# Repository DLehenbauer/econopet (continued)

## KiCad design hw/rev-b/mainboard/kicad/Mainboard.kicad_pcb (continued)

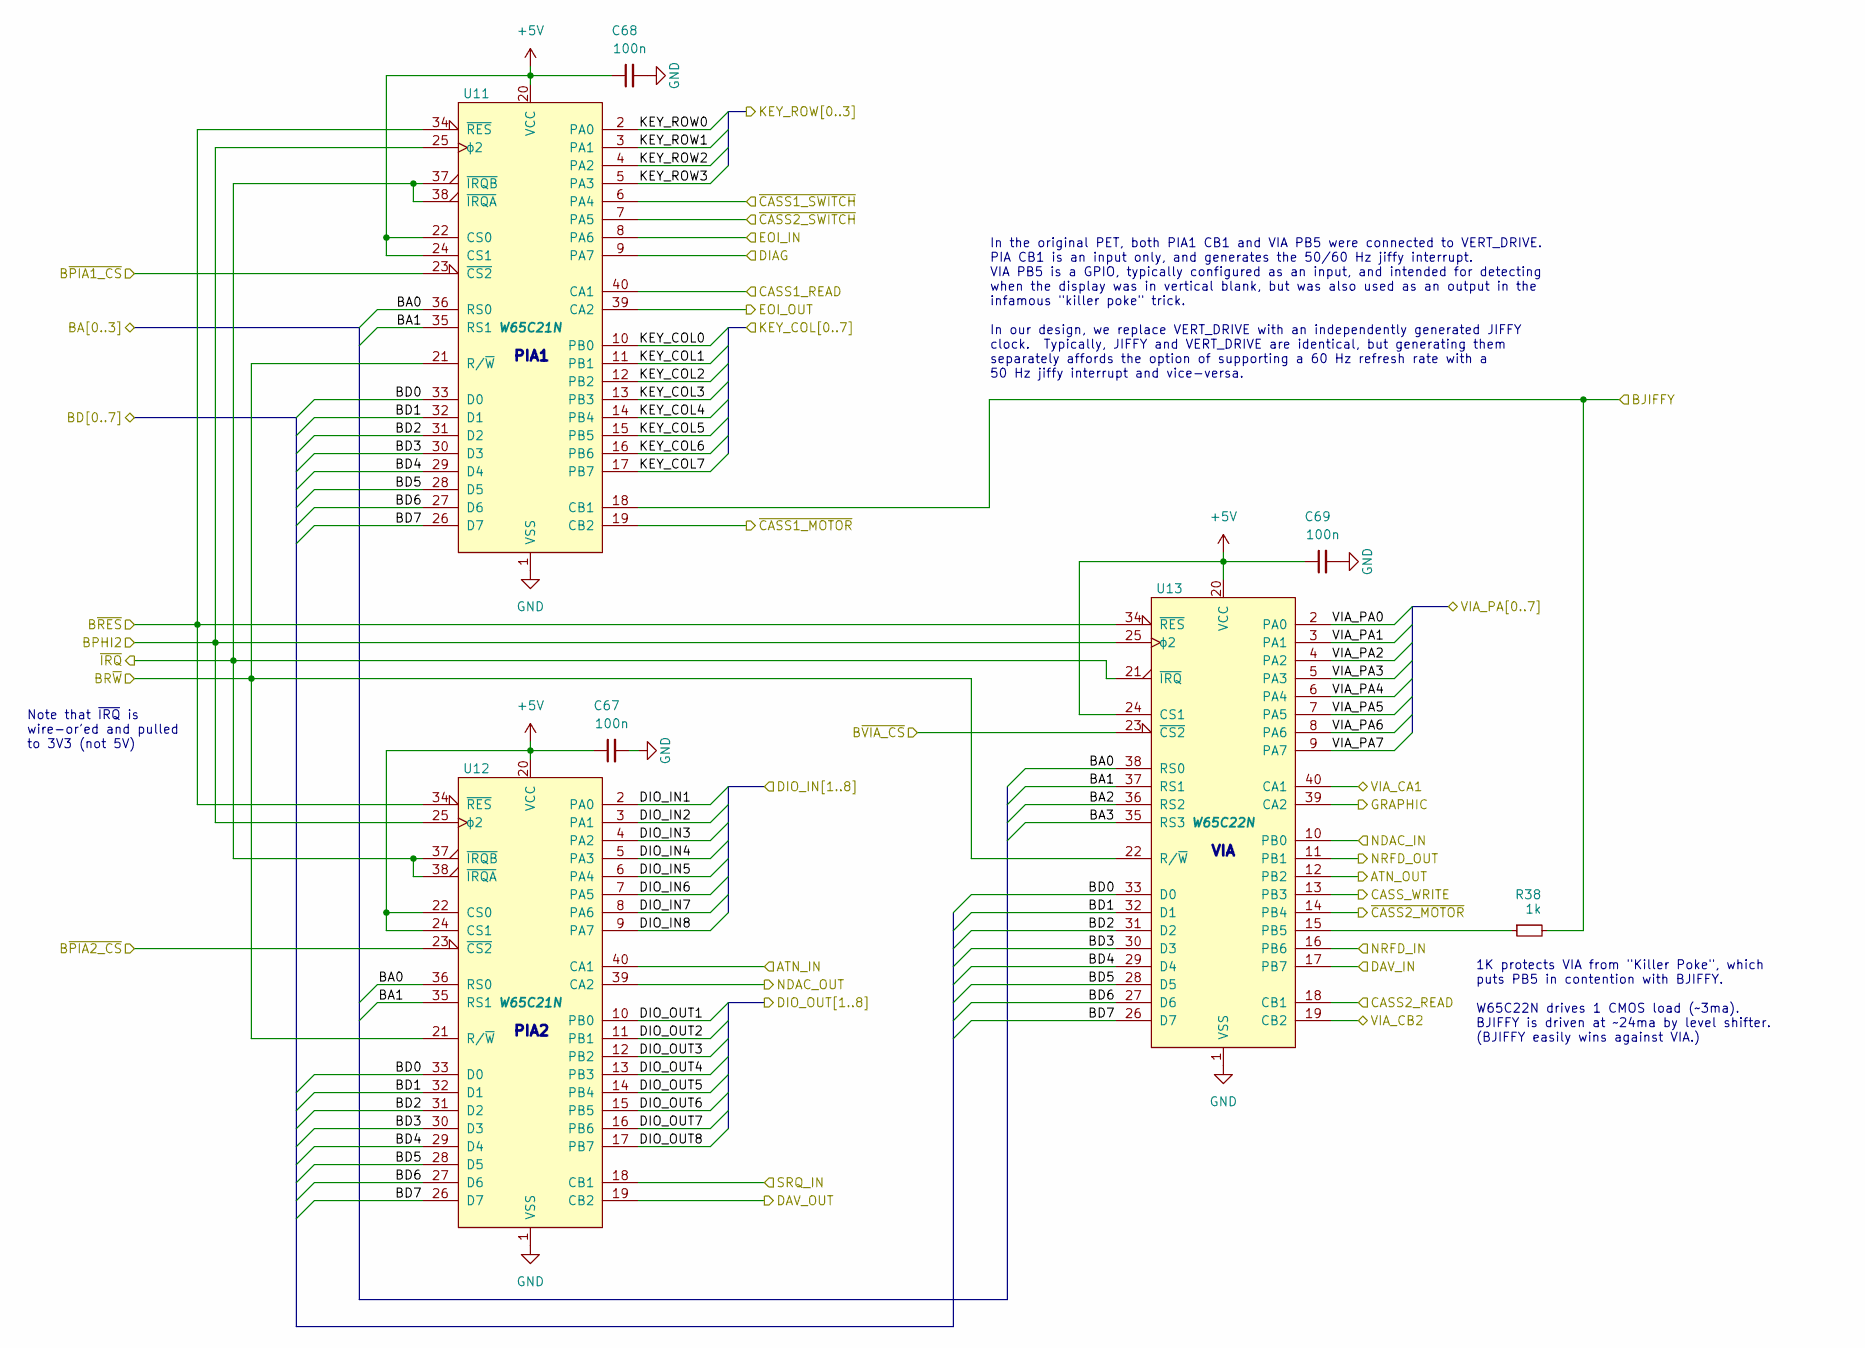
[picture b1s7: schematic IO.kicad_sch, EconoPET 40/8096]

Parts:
C67, C68, C69: 100n; C_0402_1005Metric; LCSC Part # C307331
R38: 1k; R_0402_1005Metric; LCSC Part # C11702
U11, U12: W65C21N; DIP-40_W15.24mm_Socket; MOUSER 955-W65C21N6TPG-14,571-1-2199299-5
U13: W65C22N; DIP-40_W15.24mm_Socket; MOUSER 955-W65C22N6TPG-14,571-1-2199299-5

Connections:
+5V: C67.1, C68.1, C69.1, U11.20 (VCC), U11.22 (CS0), U11.24 (CS1), U12.20 (VCC), U12.22 (CS0), U12.24 (CS1), U13.20 (VCC), U13.24 (CS1); also elsewhere on the board
/CASS/CASS1_READ: U11.40 (CA1); also elsewhere on the board
/CASS/CASS2_READ: U13.18 (CB1); also elsewhere on the board
/CASS/CASS_WRITE: U13.13 (PB3); also elsewhere on the board
/CASS/~CASS1_MOTOR: U11.19 (CB2); also elsewhere on the board
/CASS/~CASS1_SWITCH: U11.6 (PA4); also elsewhere on the board
/CASS/~CASS2_MOTOR: U13.14 (PB4); also elsewhere on the board
/CASS/~CASS2_SWITCH: U11.7 (PA5); also elsewhere on the board
/IEEE/ATN_IN: U12.40 (CA1); also elsewhere on the board
/IEEE/ATN_OUT: U13.12 (PB2); also elsewhere on the board
/IEEE/DAV_IN: U13.17 (PB7); also elsewhere on the board
/IEEE/DAV_OUT: U12.19 (CB2); also elsewhere on the board
/IEEE/DIO_IN1: U12.2 (PA0); also elsewhere on the board
/IEEE/DIO_IN2: U12.3 (PA1); also elsewhere on the board
/IEEE/DIO_IN3: U12.4 (PA2); also elsewhere on the board
/IEEE/DIO_IN4: U12.5 (PA3); also elsewhere on the board
/IEEE/DIO_IN5: U12.6 (PA4); also elsewhere on the board
/IEEE/DIO_IN6: U12.7 (PA5); also elsewhere on the board
/IEEE/DIO_IN7: U12.8 (PA6); also elsewhere on the board
/IEEE/DIO_IN8: U12.9 (PA7); also elsewhere on the board
/IEEE/DIO_OUT1: U12.10 (PB0); also elsewhere on the board
/IEEE/DIO_OUT2: U12.11 (PB1); also elsewhere on the board
/IEEE/DIO_OUT3: U12.12 (PB2); also elsewhere on the board
/IEEE/DIO_OUT4: U12.13 (PB3); also elsewhere on the board
/IEEE/DIO_OUT5: U12.14 (PB4); also elsewhere on the board
/IEEE/DIO_OUT6: U12.15 (PB5); also elsewhere on the board
/IEEE/DIO_OUT7: U12.16 (PB6); also elsewhere on the board
/IEEE/DIO_OUT8: U12.17 (PB7); also elsewhere on the board
/IEEE/EOI_IN: U11.8 (PA6); also elsewhere on the board
/IEEE/EOI_OUT: U11.39 (CA2); also elsewhere on the board
/IEEE/IFC_OUT: U11.34 (~RES), U12.34 (~RES), U13.34 (~RES); also elsewhere on the board
/IEEE/NDAC_IN: U13.10 (PB0); also elsewhere on the board
/IEEE/NDAC_OUT: U12.39 (CA2); also elsewhere on the board
/IEEE/NRFD_IN: U13.16 (PB6); also elsewhere on the board
/IEEE/NRFD_OUT: U13.11 (PB1); also elsewhere on the board
/IEEE/SRQ_IN: U12.18 (CB1); also elsewhere on the board
/IO/BA0: U11.36 (RS0), U12.36 (RS0), U13.38 (RS0); also elsewhere on the board
/IO/BA1: U11.35 (RS1), U12.35 (RS1), U13.37 (RS1); also elsewhere on the board
/IO/BA2: U13.36 (RS2); also elsewhere on the board
/IO/BA3: U13.35 (RS3); also elsewhere on the board
/IO/BD0: U11.33 (D0), U12.33 (D0), U13.33 (D0); also elsewhere on the board
/IO/BD1: U11.32 (D1), U12.32 (D1), U13.32 (D1); also elsewhere on the board
/IO/BD2: U11.31 (D2), U12.31 (D2), U13.31 (D2); also elsewhere on the board
/IO/BD3: U11.30 (D3), U12.30 (D3), U13.30 (D3); also elsewhere on the board
/IO/BD4: U11.29 (D4), U12.29 (D4), U13.29 (D4); also elsewhere on the board
/IO/BD5: U11.28 (D5), U12.28 (D5), U13.28 (D5); also elsewhere on the board
/IO/BD6: U11.27 (D6), U12.27 (D6), U13.27 (D6); also elsewhere on the board
/IO/BD7: U11.26 (D7), U12.26 (D7), U13.26 (D7); also elsewhere on the board
/IO/BJIFFY: R38.2, U11.18 (CB1); also elsewhere on the board
/IO/BPHI2: U11.25 (ϕ2), U12.25 (ϕ2), U13.25 (ϕ2); also elsewhere on the board
/IO/BR~W: U11.21 (R/~W), U12.21 (R/~W), U13.22 (R/~W); also elsewhere on the board
/IO/B~PIA1_CS: U11.23 (~CS2); also elsewhere on the board
/IO/B~PIA2_CS: U12.23 (~CS2); also elsewhere on the board
/IO/B~VIA_CS: U13.23 (~CS2); also elsewhere on the board
/IO/DIAG: U11.9 (PA7); also elsewhere on the board
/IO/GRAPHIC: U13.39 (CA2); also elsewhere on the board
/IO/KEY_COL0: U11.10 (PB0); also elsewhere on the board
/IO/KEY_COL1: U11.11 (PB1); also elsewhere on the board
/IO/KEY_COL2: U11.12 (PB2); also elsewhere on the board
/IO/KEY_COL3: U11.13 (PB3); also elsewhere on the board
/IO/KEY_COL4: U11.14 (PB4); also elsewhere on the board
/IO/KEY_COL5: U11.15 (PB5); also elsewhere on the board
/IO/KEY_COL6: U11.16 (PB6); also elsewhere on the board
/IO/KEY_COL7: U11.17 (PB7); also elsewhere on the board
/IO/KEY_ROW0: U11.2 (PA0); also elsewhere on the board
/IO/KEY_ROW1: U11.3 (PA1); also elsewhere on the board
/IO/KEY_ROW2: U11.4 (PA2); also elsewhere on the board
/IO/KEY_ROW3: U11.5 (PA3); also elsewhere on the board
/IO/VIA_CA1: U13.40 (CA1); also elsewhere on the board
/IO/VIA_CB2: U13.19 (CB2); also elsewhere on the board
/IO/VIA_PA0: U13.2 (PA0); also elsewhere on the board
/IO/VIA_PA1: U13.3 (PA1); also elsewhere on the board
/IO/VIA_PA2: U13.4 (PA2); also elsewhere on the board
/IO/VIA_PA3: U13.5 (PA3); also elsewhere on the board
/IO/VIA_PA4: U13.6 (PA4); also elsewhere on the board
/IO/VIA_PA5: U13.7 (PA5); also elsewhere on the board
/IO/VIA_PA6: U13.8 (PA6); also elsewhere on the board
/IO/VIA_PA7: U13.9 (PA7); also elsewhere on the board
/MAGIC/FPGA/~IRQ: U11.37 (~IRQB), U11.38 (~IRQA), U12.37 (~IRQB), U12.38 (~IRQA), U13.21 (~IRQ); also elsewhere on the board
GND: C67.2, C68.2, C69.2, U11.1 (VSS), U12.1 (VSS), U13.1 (VSS); also elsewhere on the board
unnamed: R38.1, U13.15 (PB5)

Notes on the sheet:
1K protects VIA from "Killer Poke", which puts PB5 in contention with BJIFFY. W65C22N drives 1 CMOS load (~3ma). BJIFFY is driven at ~24ma by level shifter. (BJIFFY easily wins against VIA.)
In the original PET, both PIA1 CB1 and VIA PB5 were connected to VERT_DRIVE. PIA CB1 is an input only, and generates the 50/60 Hz jiffy interrupt. VIA PB5 is a GPIO, typically configured as an input, and intended for detecting when the display was in vertical blank, but was also used as an output i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
PIA1
PIA2
Note that ~{IRQ} is wire-or'ed and pulled to 3V3 (not 5V)
VIA

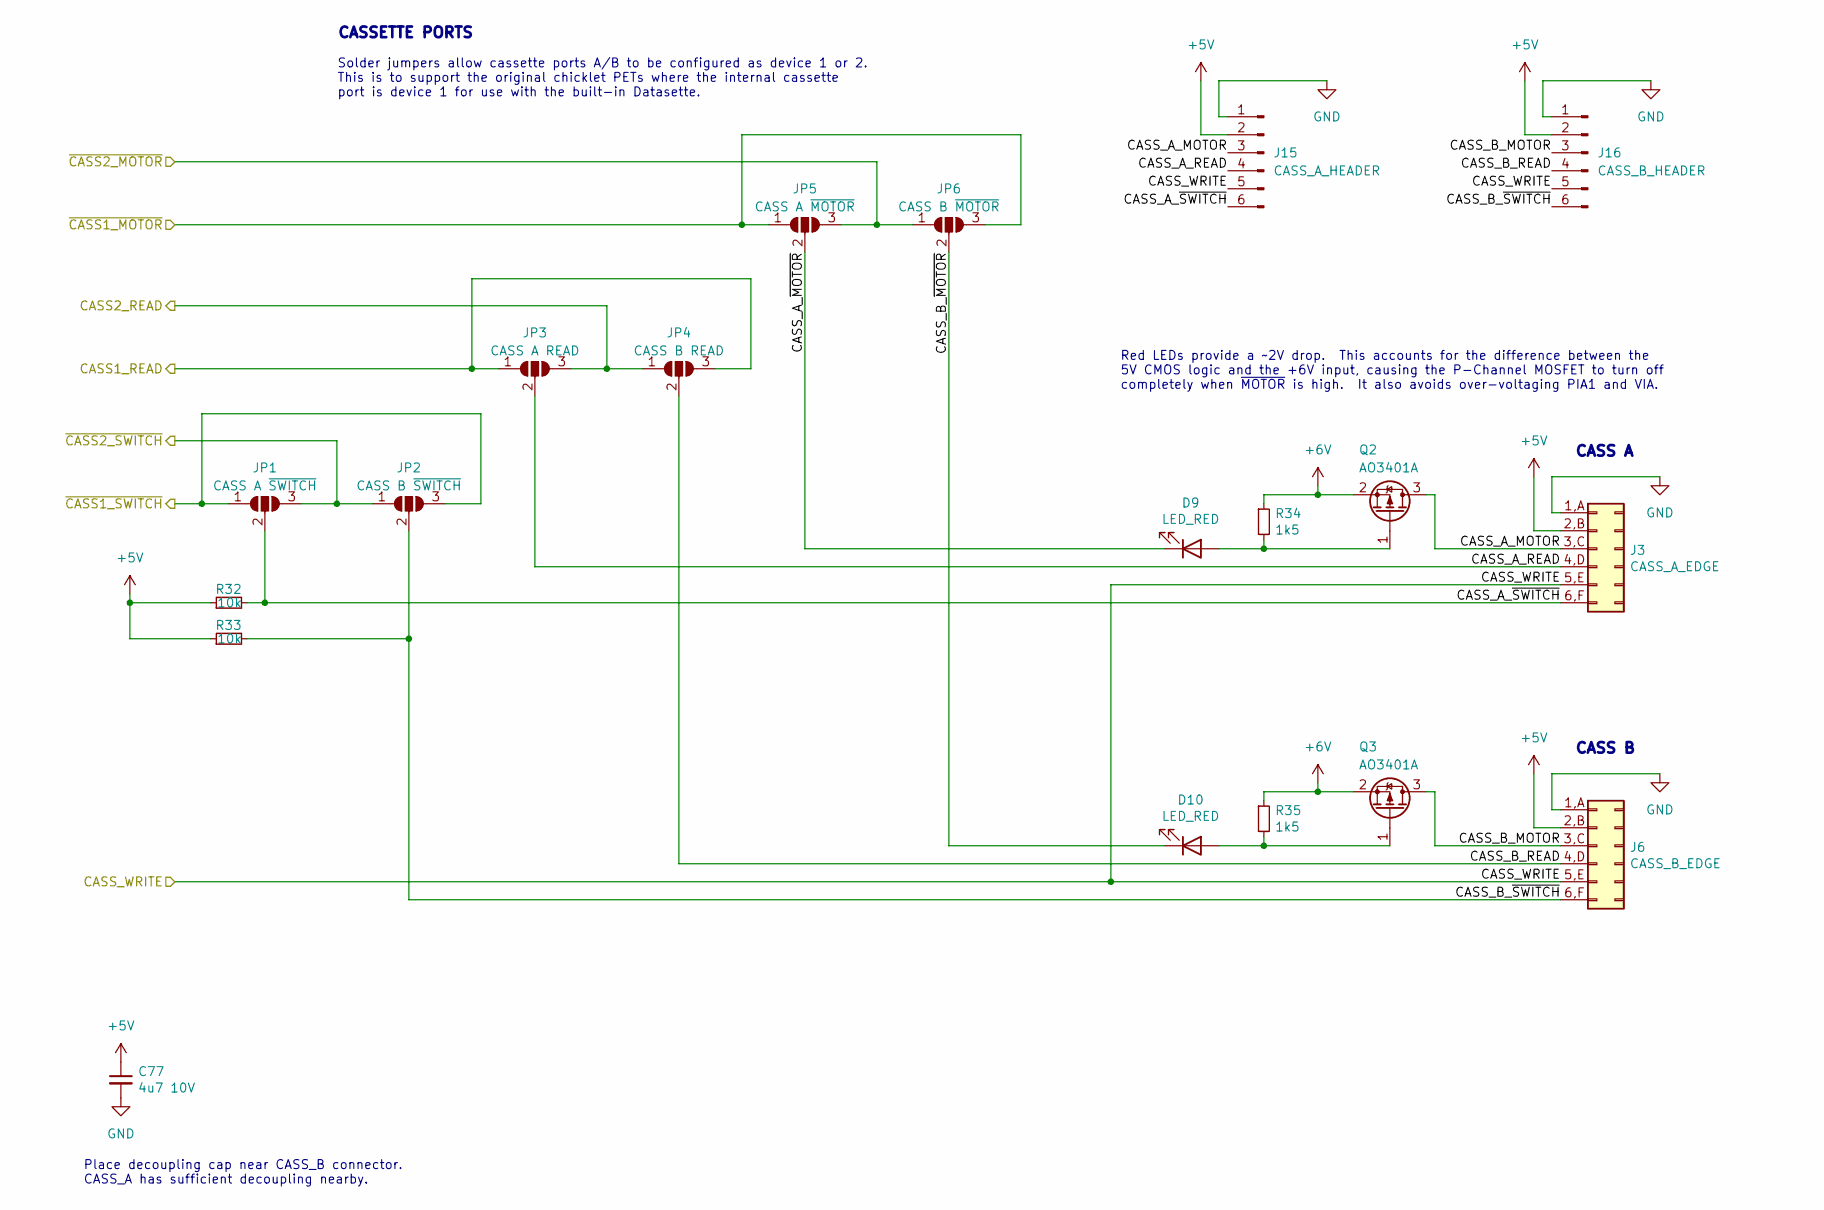
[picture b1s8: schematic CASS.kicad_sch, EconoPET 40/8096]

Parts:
C77: 4u7 10V; C_0402_1005Metric; LCSC Part # C23733
D9, D10: LED_RED; LED_0603_1608Metric; LCSC Part # C2286
J3: CASS_A_EDGE; CBM_PET_CASS_EDGE_CON_12P
J6: CASS_B_EDGE; CBM_PET_CASS_EDGE_CON_12P
J15: CASS_A_HEADER; PinHeader_1x06_P2.54mm_Vertical; MOUSER 649-1012937891002BLF
J16: CASS_B_HEADER; PinHeader_1x06_P2.54mm_Vertical; MOUSER 649-1012937891002BLF
JP1: CASS A ~{SWITCH}; SolderJumper-3_P1.3mm_Open_RoundedPad1.0x1.5mm
JP2: CASS B ~{SWITCH}; SolderJumper-3_P1.3mm_Open_RoundedPad1.0x1.5mm
JP3: CASS A READ; SolderJumper-3_P1.3mm_Open_RoundedPad1.0x1.5mm
JP4: CASS B READ; SolderJumper-3_P1.3mm_Open_RoundedPad1.0x1.5mm
JP5: CASS A ~{MOTOR}; SolderJumper-3_P1.3mm_Open_RoundedPad1.0x1.5mm
JP6: CASS B ~{MOTOR}; SolderJumper-3_P1.3mm_Open_RoundedPad1.0x1.5mm
Q2, Q3: AO3401A; SOT-23_L2.9-W1.3-P1.90-LS2.4-BR; LCSC Part # C15127
R32, R33: 10k; R_0402_1005Metric; LCSC Part # C25744
R34, R35: 1k5; R_0402_1005Metric; LCSC Part # C25867

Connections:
+5V: C77.1, J3.2,B (+5V), J6.2,B (+5V), J15.2, J16.2, R32.1, R33.1; also elsewhere on the board
+6V: Q2.2 (S), Q3.2 (S), R34.1, R35.1; also elsewhere on the board
/CASS/CASS1_READ: JP3.1 (A), JP4.3 (B); also elsewhere on the board
/CASS/CASS2_READ: JP3.3 (B), JP4.1 (A); also elsewhere on the board
/CASS/CASS_A_MOTOR: J3.3,C (MOTOR), J15.3, Q2.3 (D)
/CASS/CASS_A_READ: J3.4,D (READ), J15.4, JP3.2 (C)
/CASS/CASS_A_~MOTOR: D9.1 (K), JP5.2 (C)
/CASS/CASS_A_~SWITCH: J3.6,F (SWITCH), J15.6, JP1.2 (C), R32.2
/CASS/CASS_B_MOTOR: J6.3,C (MOTOR), J16.3, Q3.3 (D)
/CASS/CASS_B_READ: J6.4,D (READ), J16.4, JP4.2 (C)
/CASS/CASS_B_~MOTOR: D10.1 (K), JP6.2 (C)
/CASS/CASS_B_~SWITCH: J6.6,F (SWITCH), J16.6, JP2.2 (C), R33.2
/CASS/CASS_WRITE: J3.5,E (WRITE), J6.5,E (WRITE), J15.5, J16.5; also elsewhere on the board
/CASS/~CASS1_MOTOR: JP5.1 (A), JP6.3 (B); also elsewhere on the board
/CASS/~CASS1_SWITCH: JP1.1 (A), JP2.3 (B); also elsewhere on the board
/CASS/~CASS2_MOTOR: JP5.3 (B), JP6.1 (A); also elsewhere on the board
/CASS/~CASS2_SWITCH: JP1.3 (B), JP2.1 (A); also elsewhere on the board
GND: C77.2, J3.1,A (GND), J6.1,A (GND), J15.1, J16.1; also elsewhere on the board
unnamed: D9.2 (A), Q2.1 (G), R34.2
unnamed: D10.2 (A), Q3.1 (G), R35.2

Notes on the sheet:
Solder jumpers allow cassette ports A/B to be configured as device 1 or 2. This is to support the original chicklet PETs where the internal cassette port is device 1 for use with the built-in Datasette.
CASS B
Red LEDs provide a ~2V drop. This accounts for the difference between the 5V CMOS logic and the +6V input, causing the P-Channel MOSFET to turn off completely when ~{MOTOR} is high. It also avoids over-voltaging PIA1 and VIA.
CASS A
Place decoupling cap near CASS_B connector. CASS_A has sufficient decoupling nearby.
CASSETTE PORTS

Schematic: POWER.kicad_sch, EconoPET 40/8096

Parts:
C7, C14, C18, C25, C27, C28, C89: 100n; C_0402_1005Metric; LCSC Part # C307331
C9, C10, C85: 22n; C_0402_1005Metric; LCSC Part # C1532
C11, C19, C22, C24, C29: 22u; C_0805_2012Metric; LCSC Part # C45783
C12, C13, C15, C16: 10u; C_0603_1608Metric; LCSC Part # C96446
C17, C21: 33p; C_0402_1005Metric; LCSC Part # C1562
C20: 1u; C_0402_1005Metric; LCSC Part # C52923
C23, C26, C30, C31: 4u7 10V; C_0402_1005Metric; LCSC Part # C23733
C108, C109: 10u 16V; CP_EIA-3216-18_Kemet-A; LCSC Part # C7171
C110: 15000uF; CP_Radial_D18.0mm_P5.00mm_P7.50mm; MOUSER 661-BV250L153AM40S; not fitted
C111, C112: 2200uF; CP_Radial_D12.5mm_P5.00mm; MOUSER 232-25PK2200MEFC125X
D1, D2, D3: SS54; D_SMA; LCSC Part # C22452
D4: SM4007; D_SOD-123F; LCSC Part # C64898
D6: LED_RED; LED_0603_1608Metric; LCSC Part # C2286
FB1: 600 200ma; L_0603_1608Metric; LCSC Part # C1002
H1: MountingHole_Pad; MountingHole_4mm_Pad
J8: PET POWER; PET_POWER_Molex_KK-396_A-41791-0009_1x09_P3.96mm_Vertical; MOUSER 571-6403849
J10: 5V PWR; PinHeader_2x03_P2.54mm_Vertical; MOUSER 649-1012938195002BLF
J11: 9V POWER; PinHeader_1x02_P2.54mm_Vertical; MOUSER 649-1012937891002BLF
J13: 9V POWER JACK; BarrelJack_Horizontal; MOUSER 806-KLDX-0202-B
J27: 6V POWER; PinHeader_1x02_P2.54mm_Vertical; MOUSER 649-1012937891002BLF
J28: 5V POWER; PinHeader_1x02_P2.54mm_Vertical; MOUSER 649-1012937891002BLF
L1, L2: 1.8uH; IND-SMD_L5.0-W5.0_FNR50XXS; LCSC Part # C167956
R5, R12: 120; R_0805_2012Metric; LCSC Part # C17437
R6: 12k; R_0402_1005Metric; LCSC Part # C25752
R7: 2k2; R_0402_1005Metric; LCSC Part # C25879
R8: 120k; R_0603_1608Metric; LCSC Part # C25808
R9: 13k; R_0603_1608Metric; LCSC Part # C22797
R10: 330; R_0603_1608Metric; LCSC Part # C23138
R11: 22k; R_0402_1005Metric; LCSC Part # C25768
R13: 4k7; R_0402_1005Metric; LCSC Part # C25900
R14, R16: 330k; R_0603_1608Metric; LCSC Part # C23137
R15: 68k; R_0603_1608Metric; LCSC Part # C23231
R17: 1k5; R_0402_1005Metric; LCSC Part # C25867
R76: 150; R_0805_2012Metric; LCSC Part # C17471
R81: 33K; R_0402_1005Metric; LCSC Part # C25779
U3: AMS1117-3.3; SOT-223-3_TabPin2; LCSC Part # C6186
U4, U6: TPS564247DRLR; SOT-563; MPN TPS564242DRLR; LCSC Part # C5244316
U5: LM317AG-TN3-R; TO-252-2; LCSC Part # C75510

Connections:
+1V2: C20.1, D4.2 (A), FB1.2, R12.1, U5.2 (VO); also elsewhere on the board
+3V3: C108.1, C109.1, R10.1, U3.2 (VO); also elsewhere on the board
+5V: C11.1, C14.2, C21.1, C22.1, C24.1, C26.1, C28.1, C31.1, D4.1 (K), J10.2, J10.4, J10.6, J28.2, L1.2, R14.1, R16.1, R17.1, U3.3 (VI), U5.3 (VI); also elsewhere on the board
+6V: C17.1, C19.1, C29.1, C30.1, C89.1, J27.2, L2.2, R8.1; also elsewhere on the board
+9V_Unreg: C7.1, C12.1, C13.1, C15.1, C16.1, C18.1, C110.1, C111.1, C112.1, J8.2 (9V_IN), J11.2, J13.1, R6.2, R11.1, U4.1 (VIN), U6.1 (VIN)
/POWER/9V_UNFILT: C9.2, C10.1, C85.2, D1.1 (K), D2.1 (K), D3.1 (K), J8.4 (9V_OUT)
/POWER/VAC1: C9.1, D2.2 (A), J8.1 (AC1)
/POWER/VAC2: C10.2, D3.2 (A), J8.5 (AC2)
CHASSIS_GND: H1.1, R5.1, R76.1; also elsewhere on the board
FPGA_VCCA: C23.1, C25.1, C27.1, FB1.1; also elsewhere on the board
GND: C7.2, C11.2, C12.2, C13.2, C14.1, C15.2, C16.2, C18.2, C19.2, C20.2, C22.2, C23.2, C24.2, C25.2, C26.2, C27.2, C28.2, C29.2, C30.2, C31.2, C85.1, C89.2, C108.2, C109.2, C110.2, C111.2, C112.2, D1.2 (A), D6.1 (K), J8.3 (GND), J10.1, J10.3, J10.5, J11.1, J13.2, J13.3, J27.1, J28.1, R5.2, R7.2, R9.2, R10.2, R12.2, R13.2, R15.2, R76.2, R81.2, U3.1 (GND), U4.3 (GND), U4.4 (AGND), U5.1 (ADJ), U6.3 (GND), U6.4 (AGND); also elsewhere on the board
unnamed: D6.2 (A), R17.2
unnamed: R6.1, R7.1, U4.5 (EN)
unnamed: C17.2, R8.2, R9.1, U4.6 (FB)
unnamed: L2.1, U4.2 (SW)
unnamed: R11.2, R13.1, U6.5 (EN)
unnamed: C21.2, R14.2, R15.1, R16.2, R81.1, U6.6 (FB)
unnamed: L1.1, U6.2 (SW)

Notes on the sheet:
LM317A: ΔV_{OUT}=~3V (at ≥ 10ma) Use 120Ω load resistor T20Q144 VCORE Requirements Typical: 1.15V ~ 1.25V, Absolute max: 1.42V
18.3 VAC C.T. arrives on pins 1/5. Rectified DC leaves on pin 4, is externally smoothed by a 17-23mF capacitor and returns on pin 2. Despite being labeled 9V_UNREG in the CBM schematics, the actual voltage is closer to 12V. Pins 8/9 are not used by the replacement board. The PET power supply delive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
Power Indicator
+9V_UNREG
+9V Unreg Supply
Configurable PS filtering caps
Power Headers
FPGA_VCCA is the analog VCORE source for PLLs
AMS1117-3.3: ΔV_{OUT}=1.3V I_{L(MIN)}=10ma Use 330Ω load resistor
+5V Supply
Mounting Holes
120 Ω ∥ 150 Ω ≈ 66.7 Ω (1%) is within tolerance of CBM/PET 68 Ω (5%) Effective 0.225W ≈ original 1/4W
+1.25V Supply
+6V Supply
+3.3V Supply
Max load of ~400ma observed with a black C2N when motor is stalled at end-of-tape during rewind. 6.1V @ 1A allows 400ma per cassette port with some headroom. Voltage is non-critical as the datasette speed is controlled by a mechanical governor.
AMS1117 datasheet specifies 22u tant, but does not state a required ESR range for stability. TI LM1117 specifies 0.3-22Ω. Each C_{OUT} is 3Ω @ 100kHz (for 1.5Ω in parallel). AMS1117 internal protection diodes sufficient with output caps < 1000uF

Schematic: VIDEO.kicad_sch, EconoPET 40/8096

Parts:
J7: VIDEO; PET_Video; MOUSER 649-1012937893603BLF

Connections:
/MAGIC/BHORIZ: J7.5 (HORIZ); also elsewhere on the board
/MAGIC/BVERT: J7.3 (VERT); also elsewhere on the board
/MAGIC/BVIDEO: J7.1 (GND); also elsewhere on the board
GND: J7.2 (GND), J7.4 (GND), J7.7 (VIDEO); also elsewhere on the board

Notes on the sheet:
Not too much to see here. :-) If you're looking for the modern DVI video output over an HDMI connector, look under Magic / MCU / DVI.
VIDEO HEADER

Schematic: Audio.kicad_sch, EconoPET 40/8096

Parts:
C8, C84: 47u 10V; C_1206_3216Metric; LCSC Part # C96123
C80, C114, C115: 1u; C_0402_1005Metric; LCSC Part # C52923
C81, C116: 22n; C_0402_1005Metric; LCSC Part # C1532
C82: 68n; C_0603_1608Metric; LCSC Part # C31658
C83, C106, C107: 100n; C_0402_1005Metric; LCSC Part # C307331
C105: 47n; C_0603_1608Metric; LCSC Part # C1622
C113: 22u; C_0805_2012Metric; LCSC Part # C45783
D13, D14: 1N4148WS; D_SOD-323; LCSC Part # C2128
J21: AUDIO; CUI_SJ-43504-SMT-TR; MOUSER 490-SJ-43504-SMT-TR
LS1: 42Ω SPK; AT1220TT9R; MOUSER 665-AT1220TT9R
Q4, Q5, Q6: SS8050; SOT-23; LCSC Part # C2150
Q7: SS8550; SOT-23; LCSC Part # C8542
R36, R75: 12k; R_0402_1005Metric; LCSC Part # C25752
R37: 22k; R_0402_1005Metric; LCSC Part # C25768
R67, R69: 1k5; R_0402_1005Metric; LCSC Part # C25867
R68: 680; R_0402_1005Metric; LCSC Part # C25130
R70: 10k; R_0402_1005Metric; LCSC Part # C25744
R71: 100k; R_0402_1005Metric; LCSC Part # C25741
R72, R73: 1; R_0603_1608Metric; LCSC Part # C22936
R74: 1k; R_0402_1005Metric; LCSC Part # C11702

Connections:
+6V: C106.1, C107.1, C113.1, C114.1, Q6.3 (C), R70.1, R74.1; also elsewhere on the board
/AUDIO/~AUDIO_DET: J21.4; also elsewhere on the board
/MAGIC/FPGA/AUDIO_L: C115.1; also elsewhere on the board
/MAGIC/FPGA/AUDIO_R: C80.1; also elsewhere on the board
GND: C81.2, C83.2, C106.2, C107.2, C113.2, C114.2, C116.2, J21.1, LS1.2, Q4.2 (E), Q5.2 (E), Q7.3 (C), R68.1; also elsewhere on the board
unnamed: C8.1, C84.1, R71.1, R72.2, R73.1
unnamed: C8.2, C84.2, LS1.1
unnamed: C80.2, R36.1
unnamed: C81.1, J21.3, R36.2
unnamed: C83.1, R67.2, R69.1
unnamed: C82.2, C105.2, R68.2
unnamed: C115.2, R75.1
unnamed: C116.1, J21.2, R75.2
unnamed: D13.2 (A), Q6.1 (B), R74.2
unnamed: D13.1 (K), D14.2 (A)
unnamed: D14.1 (K), Q5.3 (C), Q7.1 (B)
unnamed: J21.5, J21.6, Q4.1 (B), R37.1
unnamed: C82.1, Q4.3 (C), R37.2, R67.1, R70.2
unnamed: C105.1, Q5.1 (B), R69.2, R71.2
unnamed: Q6.2 (E), R72.1
unnamed: Q7.2 (E), R73.2

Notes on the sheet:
Audio
Twin-T notch filter compensates for 2 KHz resonant frequency of our chosen speaker.
PET CB2 and DIAG are connected to FPGA inputs elsewhere in the schematic and are therefore not shown on this page. Within the FPGA, DIAG gates the CB2 sound signal, replacing the external AND gate used in the original PET circuitry. The FPGA then mixes the gated PET CB2 audio with the FPGA-implemen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

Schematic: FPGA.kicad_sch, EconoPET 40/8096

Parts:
C39, C41, C42, C43: 1u; C_0402_1005Metric; LCSC Part # C52923
C40, C44, C45, C46, C47, C48, C49, C50, C51, C52, C53, C55, C57, C59: 100n; C_0402_1005Metric; LCSC Part # C307331
C54, C56, C58, C60, C61: 10n; C_0402_1005Metric; LCSC Part # C15195
C62, C63, C64, C65, C66: 4u7 10V; C_0402_1005Metric; LCSC Part # C23733
D7: LED_GRN; LED_0603_1608Metric; LCSC Part # C2986059
D8: LED_RED; LED_0603_1608Metric; LCSC Part # C2286
J4: BUS_EXPANSION; PinHeader_2x25_P2.54mm_Vertical; MOUSER 649-1012938195002BLF
J9: FPGA_MCU; PinHeader_2x10_P2.54mm_Vertical; MOUSER 649-1012938195002BLF
J17: PMOD1; PMOD_Socket_2x06_P2.54mm_Horizontal; MOUSER 710-613012243121
J18: PMOD2; PMOD_Socket_2x06_P2.54mm_Horizontal; MOUSER 710-613012243121
J22: PROG; IDC-Header_2x08_P2.54mm_Vertical; MOUSER 710-61201621621
Q1: MMBT3904; SOT-23; LCSC Part # C20526
R24, R28: 100k; R_0402_1005Metric; LCSC Part # C25741
R25: 10k; R_0402_1005Metric; LCSC Part # C25744
R26: 12k; R_0402_1005Metric; LCSC Part # C25752
R27, R29: 1k; R_0402_1005Metric; LCSC Part # C11702
RN9, RN10: 10kx4; R_Array_Convex_4x0603; LCSC Part # C29718
SW3: CONFIG; SW_DIP_SPSTx03_Slide_6.7x9.18mm_W7.62mm_P2.54mm_LowProfile_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; MOUSER 490-DS04-254-1L-03BK
U10: T20Q144C3; LQFP-144_20x20mm_P0.5mm; DIGI-KEY 2134-T8Q144C3-ND

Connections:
+1V2: C39.1, C42.1, C44.1, C46.1, C48.1, C50.1, C52.1, C54.1, C56.1, C58.1, U10.13 (VCC), U10.22 (VCC), U10.49 (VCC), U10.57 (VCC), U10.85 (VCC), U10.96 (VCC), U10.125 (VCC), U10.128 (VCC), U10.130 (VCC); also elsewhere on the board
+3V3: C41.1, C43.1, C45.1, C47.1, C49.1, C51.1, C53.1, C55.1, C57.1, C59.1, C60.1, C61.1, C62.1, C63.1, C64.1, C65.1, J4.3, J9.2, J17.6, J17.12, J18.6, J18.12, R25.2, R27.2, R29.2, RN9.5 (R4.2), RN9.6 (R3.2), RN9.7 (R2.2), RN9.8 (R1.2), RN10.5 (R4.2), RN10.6 (R3.2), RN10.7 (R2.2), RN10.8 (R1.2), U10.12 (VCCIO1C_1D), U10.21 (VCCIO1B), U10.23 (VCCIO1A), U10.51 (VCCIO4B), U10.52 (VCCIO4B), U10.62 (VCCIO4A), U10.63 (VCCIO4A), U10.88 (VCCIO3E), U10.91 (VCCIO3D), U10.95 (VCCIO3B_3C), U10.122 (VCCIO3A), U10.143 (VCCIO1E); also elsewhere on the board
+5V: C66.1, J4.2, J22.10; also elsewhere on the board
/AUDIO/~AUDIO_DET: U10.20 (GPIOL_12_CDI2); also elsewhere on the board
/CPU \ RAM/A0: J4.15, U10.60 (GPIOB_RXN03); also elsewhere on the board
/CPU \ RAM/A1: J4.17, U10.65 (GPIOB_RXN07); also elsewhere on the board
/CPU \ RAM/A2: J4.19, U10.67 (GPIOB_RXP10); also elsewhere on the board
/CPU \ RAM/A3: J4.21, U10.70 (GPIOB_RXP12_EXTFB0); also elsewhere on the board
/CPU \ RAM/A4: J4.23, U10.75 (GPIOR_157_PLLIN); also elsewhere on the board
/CPU \ RAM/A5: J4.25, U10.76 (GPIOR_155); also elsewhere on the board
/CPU \ RAM/A6: J4.27, U10.82 (GPIOR_138); also elsewhere on the board
/CPU \ RAM/A7: J4.29, U10.86 (GPIOR_133_CDI18); also elsewhere on the board
/CPU \ RAM/A8: J4.31, U10.89 (GPIOR_129_CTRL10); also elsewhere on the board
/CPU \ RAM/A9: J4.33, U10.92 (GPIOR_125_CLK10); also elsewhere on the board
/CPU \ RAM/A10: J4.35, U10.97 (GPIOR_122_CLK13_CDI21); also elsewhere on the board
/CPU \ RAM/A11: J4.37, U10.99 (GPIOR_116_CTRL15); also elsewhere on the board
/CPU \ RAM/A12: J4.14, U10.59 (GPIOB_RXN02); also elsewhere on the board
/CPU \ RAM/A13: J4.16, U10.61 (GPIOB_RXP03); also elsewhere on the board
/CPU \ RAM/A14: J4.18, U10.66 (GPIOB_RXP07); also elsewhere on the board
/CPU \ RAM/A15: J4.20, U10.69 (GPIOB_RXN12_EXTFB0); also elsewhere on the board
/CPU \ RAM/D0: J4.26, U10.77 (GPIOR_154); also elsewhere on the board
/CPU \ RAM/D1: J4.28, U10.83 (GPIOR_136_CDI16); also elsewhere on the board
/CPU \ RAM/D2: J4.30, U10.87 (GPIOR_132_CDI19); also elsewhere on the board
/CPU \ RAM/D3: J4.32, U10.90 (GPIOR_128_CTRL11); also elsewhere on the board
/CPU \ RAM/D4: J4.34, U10.93 (GPIOR_123_CLK12_CDI20); also elsewhere on the board
/CPU \ RAM/D5: J4.36, U10.98 (GPIOR_117_CTRL14); also elsewhere on the board
/CPU \ RAM/D6: J4.38, U10.100 (GPIOR_113_CDI22); also elsewhere on the board
/CPU \ RAM/D7: J4.40, U10.101 (GPIOR_112_CDI23); also elsewhere on the board
/CPU \ RAM/RAM_A10: U10.84 (GPIOR_135_CDI17); also elsewhere on the board
/CPU \ RAM/RAM_A11: U10.81 (GPIOR_139); also elsewhere on the board
/CPU \ RAM/RAM_A15: U10.68 (GPIOB_RXN10); also elsewhere on the board
/CPU \ RAM/RAM_A16: J4.22, U10.71 (GPIOB_CLKP0); also elsewhere on the board
/CPU \ RAM/~ML: U10.41 (GPIOB_TXN02); also elsewhere on the board
/CPU \ RAM/~NMI: J4.11, U10.55 (GPIOB_RXP00); also elsewhere on the board
/CPU \ RAM/~RAM_OE: U10.72 (GPIOB_CLKN0); also elsewhere on the board
/CPU \ RAM/~RAM_WE: U10.58 (GPIOB_RXP02); also elsewhere on the board
/CPU \ RAM/~RES: J4.4, U10.43 (GPIOB_TXN04); also elsewhere on the board
/CPU \ RAM/~VP: U10.42 (GPIOB_TXP04); also elsewhere on the board
/MAGIC/FPGA/AUDIO_L: J9.3, U10.33 (GPIOL_05_CSO); also elsewhere on the board
/MAGIC/FPGA/AUDIO_R: J9.4, R25.1, U10.32 (GPIOL_04_CSI); also elsewhere on the board
/MAGIC/FPGA/BE: J4.9, U10.53 (GPIOB_TXP11); also elsewhere on the board
/MAGIC/FPGA/CBUS1: J4.43, RN10.2 (R2.1), U10.79 (GPIOR_150_CBUS1)
/MAGIC/FPGA/CBUS2: J4.44, RN10.1 (R1.1), U10.80 (GPIOR_149_CBUS2)
/MAGIC/FPGA/CDONE: J22.16, R28.2, RN9.4 (R4.1), U10.34 (CDONE)
/MAGIC/FPGA/CEC: J9.19, U10.6 (GPIOL_46); also elsewhere on the board
/MAGIC/FPGA/DIAG: U10.39 (GPIOB_TXN00); also elsewhere on the board
/MAGIC/FPGA/FPGA_CLK: U10.132 (GPIOL_74_PLLIN0); also elsewhere on the board
/MAGIC/FPGA/GRAPHICS: U10.40 (GPIOB_TXP02); also elsewhere on the board
/MAGIC/FPGA/HOLD: J22.15
/MAGIC/FPGA/I2C0_SCL: J9.11, U10.15 (GPIOL_24_CLK0); also elsewhere on the board
/MAGIC/FPGA/I2C0_SDA: J9.9, U10.18 (GPIOL_20_CTRL0_CDI4); also elsewhere on the board
/MAGIC/FPGA/I2C1_SCL: J9.12, U10.14 (GPIOL_25_CLK1); also elsewhere on the board
/MAGIC/FPGA/I2C1_SDA: J9.10, U10.17 (GPIOL_21_CTRL1_CDI5); also elsewhere on the board
/MAGIC/FPGA/NSTATUS: D8.1 (K), J22.11, U10.136 (GPIOL_71_NSTATUS)
/MAGIC/FPGA/PMOD1_1: J17.1, U10.135 (GPIOL_72_EXTFB0_CDI14)
/MAGIC/FPGA/PMOD1_2: J17.2, U10.131 (GPIOL_75_PLLIN1)
/MAGIC/FPGA/PMOD1_3: J17.3, U10.123 (GPIOR_77_PLLIN1)
/MAGIC/FPGA/PMOD1_4: J17.4, U10.118 (GPIOR_79_EXTFB1_CDI30)
/MAGIC/FPGA/PMOD1_5: J17.7, U10.137 (GPIOL_70_CBSEL0)
/MAGIC/FPGA/PMOD1_6: J17.8, U10.134 (GPIOL_73_EXTFB1_CDI15)
/MAGIC/FPGA/PMOD1_7: J17.9, U10.124 (GPIOR_76_PLLIN0)
/MAGIC/FPGA/PMOD1_8: J17.10, U10.119 (GPIOR_78_EXTFB0_CDI31)
/MAGIC/FPGA/PMOD2_1: J18.1, U10.4 (GPIOL_54_CDI11)
/MAGIC/FPGA/PMOD2_2: J18.2, U10.144 (GPIOL_64)
/MAGIC/FPGA/PMOD2_3: J18.3, U10.141 (GPIOL_65)
/MAGIC/FPGA/PMOD2_4: J18.4, U10.139 (GPIOL_68)
/MAGIC/FPGA/PMOD2_5: J18.7, U10.3 (GPIOL_53_CDI10)
/MAGIC/FPGA/PMOD2_6: J18.8, U10.142 (GPIOL_66_CDI12)
/MAGIC/FPGA/PMOD2_7: J18.9, U10.140 (GPIOL_67_CDI13)
/MAGIC/FPGA/PMOD2_8: J18.10, U10.138 (GPIOL_69_CBSEL1)
/MAGIC/FPGA/R94: J4.48, U10.106 (GPIOR_94_CDI27)
/MAGIC/FPGA/R95: J4.47, U10.105 (GPIOR_95_CDI26)
/MAGIC/FPGA/R104: J4.46, U10.103 (GPIOR_104_CDI25)
/MAGIC/FPGA/R105: J4.45, U10.102 (GPIOR_105_CDI24)
/MAGIC/FPGA/RDY: J4.6, U10.45 (GPIOB_TXP06); also elsewhere on the board
/MAGIC/FPGA/REF_RES: R26.2, U10.36 (REF_RES)
/MAGIC/FPGA/S1: SW3.6, U10.116 (GPIOR_81_MREFCLK)
/MAGIC/FPGA/S2: SW3.5, U10.117 (GPIOR_80)
/MAGIC/FPGA/S3: SW3.4, U10.19 (GPIOL_13_CDI3)
/MAGIC/FPGA/SPI0_RX: J9.8, U10.28 (GPIOL_09_CDI1); also elsewhere on the board
/MAGIC/FPGA/SPI0_SCK: J9.6, U10.30 (GPIOL_01_CCK); also elsewhere on the board
/MAGIC/FPGA/SPI0_TX: J9.7, U10.29 (GPIOL_08_CDI0); also elsewhere on the board
/MAGIC/FPGA/SPI0_~CS: J9.5, J22.12, U10.31 (GPIOL_00_SS_N); also elsewhere on the board
/MAGIC/FPGA/SPI1_RX: J9.20, U10.7 (GPIOL_41_CDI9); also elsewhere on the board
/MAGIC/FPGA/SPI1_SCK: J9.15, U10.11 (GPIOL_31_CLK7_CDI6); also elsewhere on the board
/MAGIC/FPGA/SPI1_TX: J9.18, U10.8 (GPIOL_40_CDI8); also elsewhere on the board
/MAGIC/FPGA/SPI1_~CS: J9.17, U10.10 (GPIOL_32_CTRL4_CDI7); also elsewhere on the board
/MAGIC/FPGA/SPI1_~READY: J9.16, U10.16 (GPIOL_22_CTRL2); also elsewhere on the board
/MAGIC/FPGA/SWCLK: J22.3; also elsewhere on the board
/MAGIC/FPGA/SWD: J22.5; also elsewhere on the board
/MAGIC/FPGA/SYNC: J4.10, U10.54 (GPIOB_TXN11); also elsewhere on the board
/MAGIC/FPGA/TCK: J22.2, RN9.1 (R1.1), U10.26 (TCK)
/MAGIC/FPGA/TDI: J22.4, RN9.2 (R2.1), U10.27 (TDI)
/MAGIC/FPGA/TDO: J22.6, U10.24 (TDO)
/MAGIC/FPGA/TEST_N: J4.41, RN10.4 (R4.1), U10.74 (GPIOR_158_TEST_N)
/MAGIC/FPGA/TMS: J22.8, RN9.3 (R3.1), U10.25 (TMS)
/MAGIC/FPGA/UART_RX: J22.7; also elsewhere on the board
/MAGIC/FPGA/UART_TX: J22.9; also elsewhere on the board
/MAGIC/FPGA/VIA_CB2: U10.38 (GPIOB_TXP00); also elsewhere on the board
/MAGIC/FPGA/~CRESET: C40.1, J22.14, R24.1, U10.35 (~CRESET); also elsewhere on the board
/MAGIC/FPGA/~IRQ: J4.5, U10.46 (GPIOB_TXN06); also elsewhere on the board
/MAGIC/FPGA/~SO: J4.8, U10.48 (GPIOB_TXN09); also elsewhere on the board
/MAGIC/FPGA/~SPI_ENA: J22.13; also elsewhere on the board
/MAGIC/HORIZ: U10.111 (GPIOR_85); also elsewhere on the board
/MAGIC/JIFFY: J4.42, RN10.3 (R3.1), U10.78 (GPIOR_151_CBUS0); also elsewhere on the board
/MAGIC/MCU/SD_~CS: J9.14; also elsewhere on the board
/MAGIC/PHI2: J4.7, U10.47 (GPIOB_TXP09); also elsewhere on the board
/MAGIC/R~W: J4.12, U10.56 (GPIOB_RXN00); also elsewhere on the board
/MAGIC/VERT: U10.110 (GPIOR_87_CDI29); also elsewhere on the board
/MAGIC/VIDEO: U10.109 (GPIOR_88_CDI28); also elsewhere on the board
/MAGIC/~IO_OE: U10.115 (GPIOR_82); also elsewhere on the board
/MAGIC/~PIA1_CS: U10.112 (GPIOR_86); also elsewhere on the board
/MAGIC/~PIA2_CS: U10.114 (GPIOR_83); also elsewhere on the board
/MAGIC/~VIA_CS: U10.113 (GPIOR_84); also elsewhere on the board
FPGA_VCCA: U10.2 (VCCA_TL), U10.73 (VCCA_BR), U10.107 (VCCA_TR); also elsewhere on the board
GND: C39.2, C40.2, C41.2, C42.2, C43.2, C44.2, C45.2, C46.2, C47.2, C48.2, C49.2, C50.2, C51.2, C52.2, C53.2, C54.2, C55.2, C56.2, C57.2, C58.2, C59.2, C60.2, C61.2, C62.2, C63.2, C64.2, C65.2, C66.2, J4.1, J4.13, J4.24, J4.39, J4.49, J4.50, J9.1, J9.13, J17.5, J17.11, J18.5, J18.11, J22.1, Q1.2 (E), R24.2, R26.1, SW3.1, SW3.2, SW3.3, U10.1 (GND), U10.5 (GND), U10.9 (GND), U10.37 (GND), U10.44 (GND), U10.50 (GND), U10.64 (GND), U10.94 (GND), U10.104 (GND), U10.108 (GND), U10.120 (GND), U10.121 (GND), U10.126 (GND), U10.127 (GND), U10.129 (GND), U10.133 (GND); also elsewhere on the board
unnamed: D7.2 (A), R27.1
unnamed: D7.1 (K), Q1.3 (C)
unnamed: D8.2 (A), R29.1
unnamed: Q1.1 (B), R28.1

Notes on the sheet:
BD0
TODO: Cleanup
1% tolerance specified
BD2
BD1
NSTATUS driven low if bitstream contains wrong device ID or fails CRC check.
AD7
AD4
During configuration, GPIO pins (excluding LVDS) are configured in weak pull-up mode. LVDS are tri-stated without a pull-up or pull-down resistor. Pull ~{CRESET} low to reset FPGA until MCU is ready. Note that MCU drives ~{CRESET} through 10k resistor so it can be overridden by programmer when conn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
BD3
Minimum decoupling caps is one 100nF and one 10nF Place lowest values closest to pin.
AD5
AD6
AD3
CDONE is open drain and requires pullup to enter user mode. TDO is terminated by the programmer at the receiving end.
CDONE is an open drain output with 10k pullup. Driving LED requires a current amplifier.
